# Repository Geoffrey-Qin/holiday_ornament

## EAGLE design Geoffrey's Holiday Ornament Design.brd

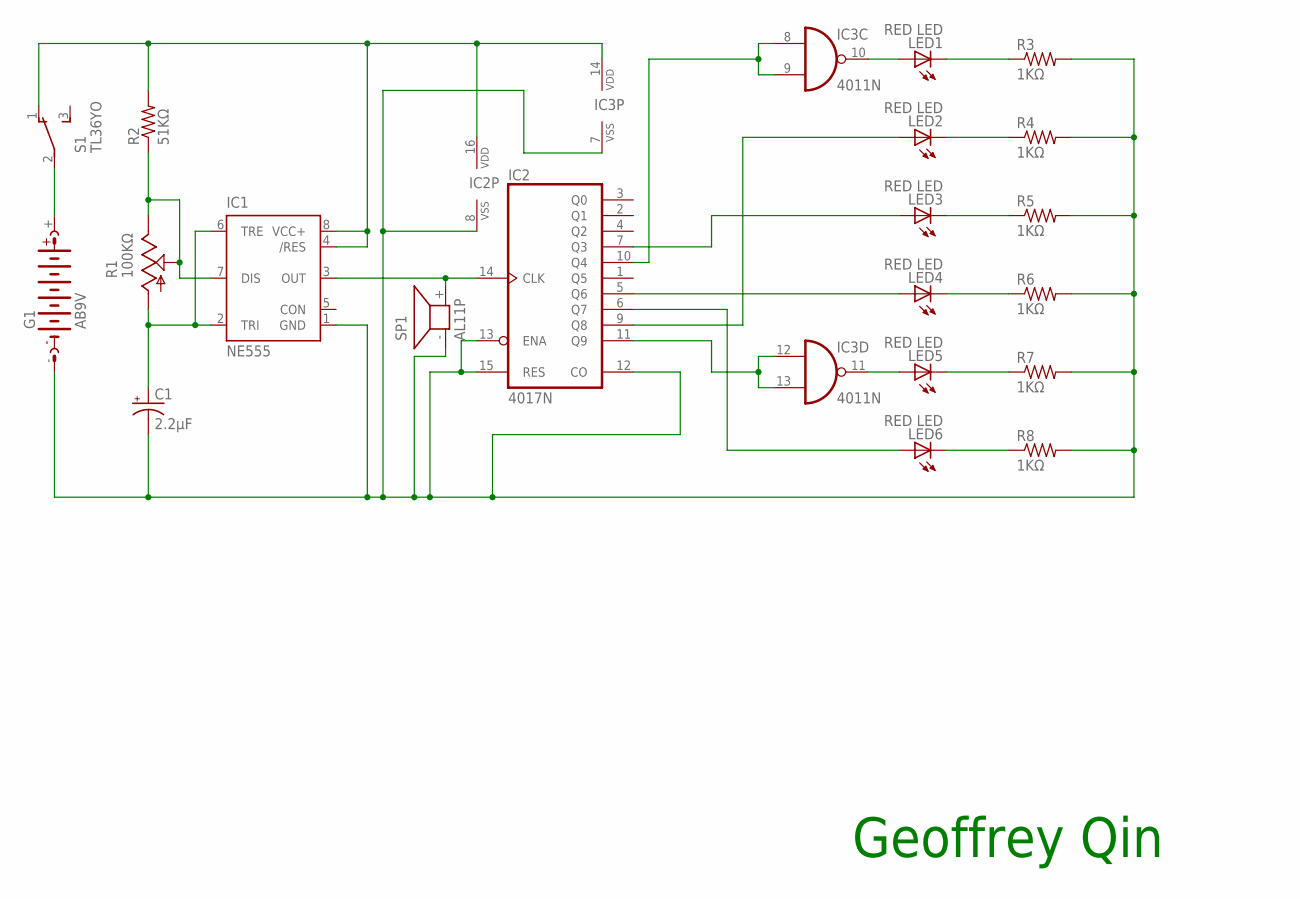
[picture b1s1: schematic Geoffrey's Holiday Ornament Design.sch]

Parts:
C1: 2.2µF; E2,5-5
G1: AB9V
IC1: NE555; DIL-08
IC2: 4017N; DIL16
IC3: 4011N; DIL14
LED1, LED2, LED3, LED4, LED5, LED6: RED LED; LED5MM
R1: 100KΩ; CA9V
R2: 51KΩ; 0207/10
R3, R4, R5, R6, R7, R8: 1KΩ; 0207/10
S1: TL36YO; TL3XYO
SP1: AL11P

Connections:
unnamed: IC3.11 (O), LED5.A
unnamed: IC1.7 (DIS), R1.E, R1.S, R2.1
unnamed: C1.-, G1.-, IC1.1 (GND), IC2.8 (VSS), IC2.12 (CO), IC2.13 (ENA), IC2.15 (RES), IC3.7 (VSS), R3.2, R4.2, R5.2, R6.2, R7.2, R8.2, SP1.- (1)
unnamed: LED6.K (C), R8.1
unnamed: LED5.K (C), R7.1
unnamed: IC1.3 (OUT), IC2.14 (CLK), SP1.+ (2)
unnamed: IC1.4 (/RES), IC1.8 (VCC+), IC2.16 (VDD), IC3.14 (VDD), R2.2, S1.1 (O)
unnamed: IC2.5 (Q6), LED4.A
unnamed: IC2.9 (Q8), LED2.A
unnamed: IC2.6 (Q7), LED6.A
unnamed: G1.+, S1.2
unnamed: IC3.10 (O), LED1.A
unnamed: C1.+, IC1.2 (TRI), IC1.6 (TRE), R1.A
unnamed: IC2.10 (Q4), IC3.8 (I0), IC3.9 (I1)
unnamed: LED4.K (C), R6.1
unnamed: LED3.K (C), R5.1
unnamed: LED2.K (C), R4.1
unnamed: LED1.K (C), R3.1
unnamed: IC2.7 (Q3), LED3.A
unnamed: IC2.11 (Q9), IC3.12 (I0), IC3.13 (I1)

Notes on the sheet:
Geoffrey Qin

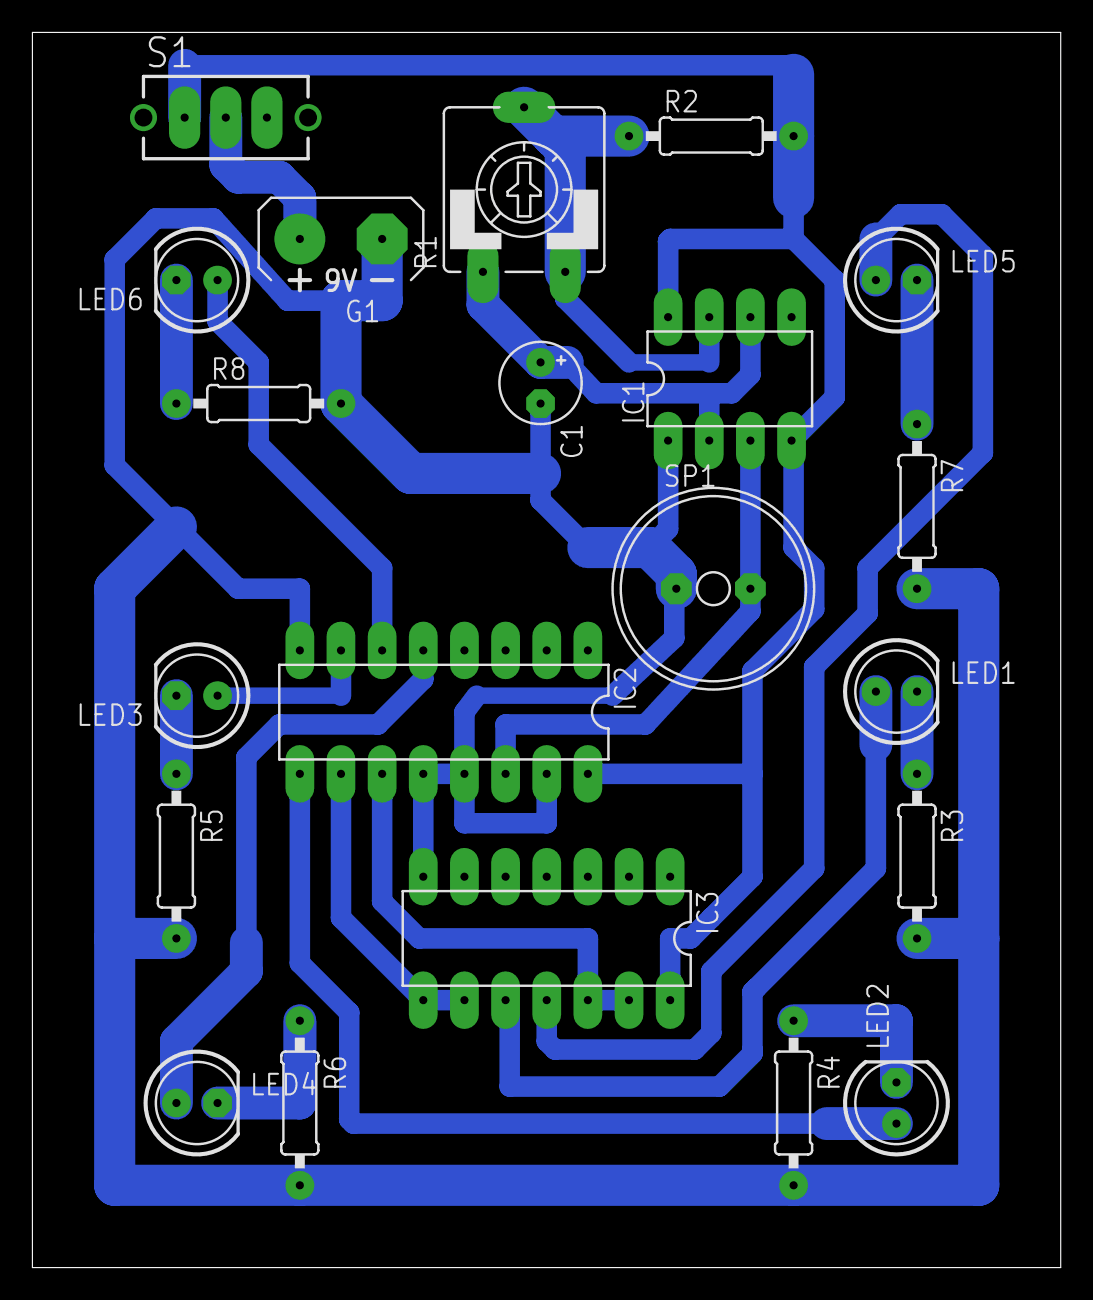
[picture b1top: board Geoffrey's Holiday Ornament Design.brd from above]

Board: 2 copper layers, 63.5 x 76.3 mm, 21 parts (0 on the bottom side), 20 nets.
